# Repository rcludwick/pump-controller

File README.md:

# pump-controller
12V pump controller

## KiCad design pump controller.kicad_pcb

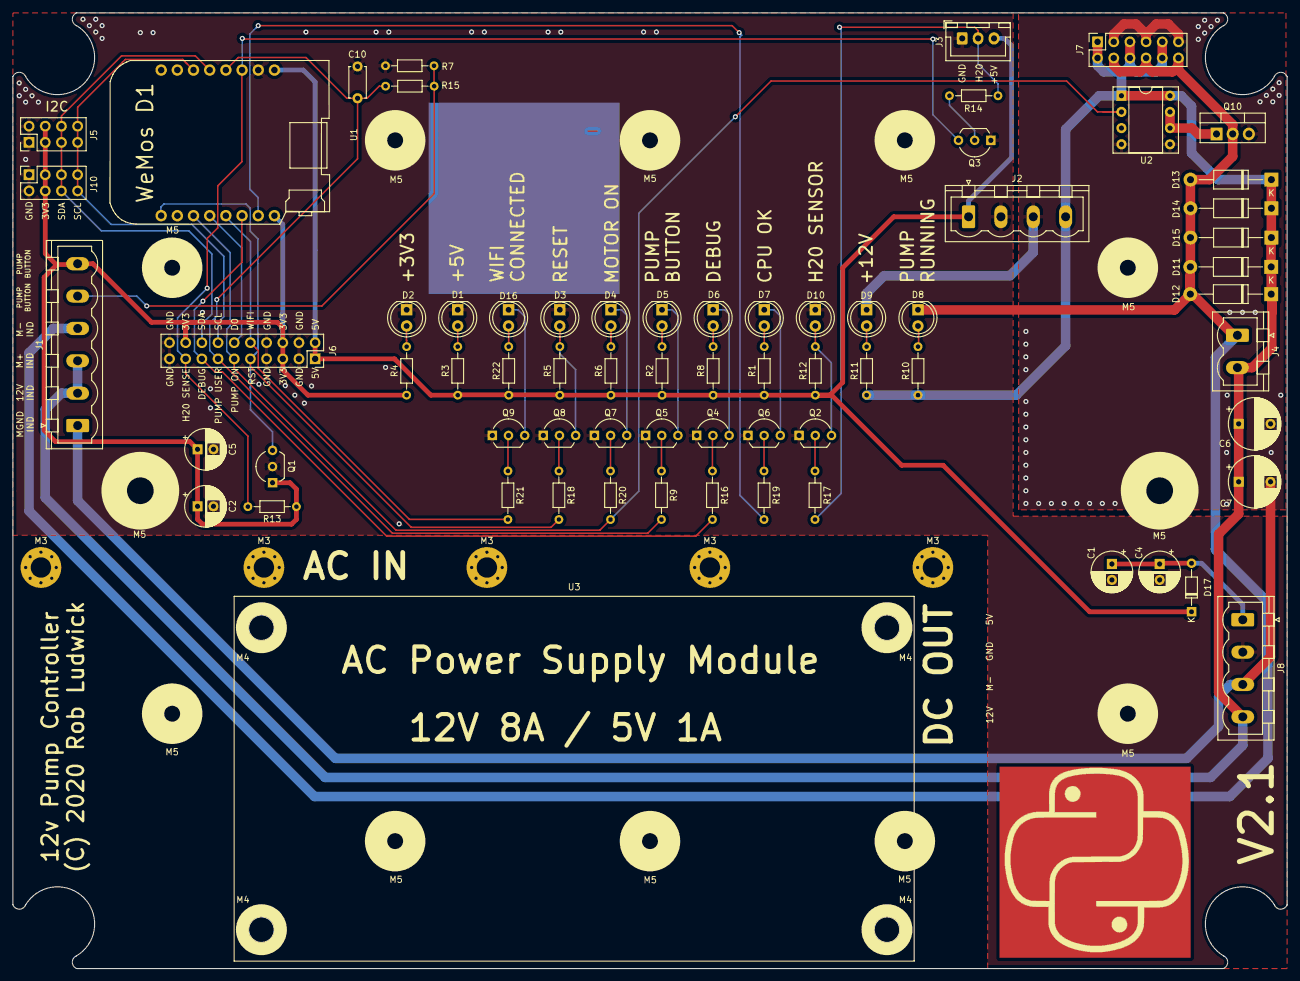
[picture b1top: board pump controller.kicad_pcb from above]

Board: 2 copper layers, 200.0 x 150.0 mm, 87 parts (1 on the bottom side), 44 nets.

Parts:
C1, C2, C4, C5: 100uf; CP_Radial_D6.3mm_P2.50mm
C6, C7: 1000uF; CP_Radial_D8.0mm_P5.00mm
C10: 22nF; C_Disc_D4.7mm_W2.5mm_P5.00mm
D1, D2, D3, D4, D5, D6, D7, D8, D9, D10, D16: LED; LED_D5.0mm
D11, D12, D13, D14, D15: D_Schottky; D_DO-41_SOD81_P12.70mm_Horizontal
D17: D_Schottky; D_DO-34_SOD68_P7.62mm_Horizontal
J1: Button Terminal; PhoenixContact_MSTBVA_2,5_6-G-5,08_1x06_P5.08mm_Vertical
J2: Power Out Terminal; PhoenixContact_MSTBVA_2,5_4-G-5,08_1x04_P5.08mm_Vertical
J3: Water Sensor Connector; JST_XH_B3B-XH-A_1x03_P2.50mm_Vertical
J4: Motor Connector; PhoenixContact_MSTBVA_2,5_2-G-5,08_1x02_P5.08mm_Vertical
J5: I2C Header 2; PinHeader_2x04_P2.54mm_Vertical
J6: Digital Connector; PinSocket_2x10_P2.54mm_Vertical
J7: Motor Connector; PinSocket_2x06_P2.54mm_Vertical
J8: Power In Terminal; PhoenixContact_MSTBVA_2,5_4-G-5,08_1x04_P5.08mm_Vertical
J10: I2C Header 1; PinSocket_2x04_P2.54mm_Vertical
M3, M3#2, M3#3, M3#4, M3#5: MountingHole_3.2mm_M3_Pad_Via
M5, M5#2, M5#3, M5#4, M5#5, M5#6, M5#7, M5#8, M5#9, M5#10: MountingHole_5mm
M5#11, M5#12: MountingHole_5x9mm
Q1: AZ7033Z-E1; TO-92_Inline_Wide
Q2, Q3, Q4, Q5, Q6, Q7, Q8, Q9: 2N3904; TO-92_Inline_Wide
Q10: VNP5N07; TO-220-3_Vertical
R1, R2, R5, R6, R8, R12, R22: 330; R_Axial_DIN0204_L3.6mm_D1.6mm_P7.62mm_Horizontal
R3, R4, R9, R10, R11, R14, R16, R17, R18, R19, R20, R21: R; R_Axial_DIN0204_L3.6mm_D1.6mm_P7.62mm_Horizontal
R7, R15: 1k; R_Axial_DIN0204_L3.6mm_D1.6mm_P7.62mm_Horizontal
R13: 10k; R_Axial_DIN0204_L3.6mm_D1.6mm_P7.62mm_Horizontal
Ref**: Val**; pythonlogo
Ref**#2: Val**; pythonlogo
U1: WeMos_mini; D1_mini_board
U2: TC4422; DIP-8_W7.62mm_Socket
U3: 12V8A_5V1A_supply

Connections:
+3V3: C2.1, C5.1, J1.6, J5.3, J5.4, J6.5, J6.6, J6.18, J10.3, J10.4, Q1.1, R4.1, R13.1, U1.16
+5V: D17.1, J2.1, J3.3, J6.1, J6.2, R1.1, R2.1, R3.1, R5.1, R6.1, R8.1, R12.1, R22.1, U1.1
+5VIN: C1.1, C4.1, D17.2, J8.1
/MOS_IN: Q10.1, U2.6, U2.7
CPU_OK: R19.2, U1.15
DEBUG: J6.15, R16.2, U1.14
MOTOR+: C6.1, C7.1, D11.1, D12.1, D13.1, D14.1, D15.1, J1.2, J1.3, J2.4, J4.2, J7.1, J7.2, J7.5, J7.6, J7.9, J7.10, J8.4, R10.1, R11.1, U2.1, U2.8
MOTOR-: D8.1, D11.2, D12.2, D13.2, D14.2, D15.2, J1.4, J4.1, J7.4, J7.8, J7.12, Q10.2
MOTOR_GND: C6.2, C7.2, D9.1, J1.1, J2.3, J7.3, J7.7, J7.11, J8.3, Q10.3, U2.4, U2.5
MOTOR_ON: J6.11, R20.2, U1.11, U2.2
unnamed: D1.2, R3.2
unnamed: D2.2, R4.2
unnamed: D3.2, Q8.3, R5.2
unnamed: D4.1, Q7.3
unnamed: D4.2, R6.2
unnamed: D5.1, Q5.3
unnamed: D5.2, R2.2
unnamed: D6.1, Q4.3
unnamed: D6.2, R8.2
unnamed: D7.1, Q6.3
unnamed: D7.2, R1.2
unnamed: D8.2, R10.2
unnamed: D9.2, R11.2
unnamed: D10.2, Q2.3, R12.2
unnamed: D16.1, Q9.3
unnamed: D16.2, R22.2
unnamed: Q2.2, R17.1
unnamed: Q3.2, R14.1
unnamed: Q4.2, R16.1
unnamed: Q5.2, R9.1
unnamed: Q6.2, R19.1
unnamed: Q7.2, R20.1
unnamed: Q8.2, R18.1
unnamed: Q9.2, R21.1
PIN_D5: J6.12, U1.12
PUMP_BUTTON: J1.5, R7.1, R15.2
PUMP_USER_SIG: C10.1, J6.13, R9.2, R15.1, U1.4
RESET: J6.9, Q1.3, R18.2, U1.9
SCL: J5.7, J5.8, J6.14, J10.7, J10.8, U1.6
SDA: J5.5, J5.6, J6.16, J10.5, J10.6, U1.5
SENSOR_OUT: J3.2, R14.2, R17.2
SIGNAL_GND: C1.2, C2.2, C4.2, C5.2, C10.2, D1.1, D2.1, D3.1, D10.1, J2.2, J3.1, J5.1, J5.2, J6.3, J6.4, J6.7, J6.8, J6.19, J6.20, J8.2, J10.1, J10.2, Q1.2, Q2.1, Q3.1, Q4.1, Q5.1, Q6.1, Q7.1, Q8.1, Q9.1, R7.2, U1.2
WATER_PRESENT: J6.17, Q3.3, R13.2, U1.3
WIFI: J6.10, R21.2, U1.13

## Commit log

2020-11-01 Added a zener diode in front of the capacitors on the 5v rail
2020-11-16 Updated debug lines. Added python logo.
2020-11-23 Added python logo.

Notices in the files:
pump controller.kicad_pcb:
(C) 2020 Rob Ludwick
